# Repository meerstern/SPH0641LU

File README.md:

# SPH0641LU
The Converter board of Kicad Data for SPH0641LU

## 概要
Syntiant社製の[デジタル出力MEMSマイクSPH0641LU4H-1][1]を2.54mmピッチへ変換する基板です。  
可聴音から超音波(100Hz～80kHz)までの幅広い帯域を高感度にセンシングすることが可能です。  
超音波センサや超音波通信などに使用可能です。  
マイク穴は基板裏面の丸印部分です。  

電源電圧1.62V~3.6V、PDMデジタル出力  
セレクトピンをプルアップする場合はR2、プルダウンする場合はR1にチップ抵抗を取り付けてください。  
※接続先がDFSDMやI2S、SPI通信等のPDMマスタに対応している必要があります。　　

## 超音波マイク比較
 用途に応じて様々な製品をラインアップしています  
| 製品名 | インタフェース | アンプ搭載有無 | 用途 | 
|:-----------|:------------|:------------|:------------|
| [アナログ出力マイク][A] | アナログ | 無 | 任意のアンプ回路を使用したい場合 | 
| [可変アンプ内蔵アナログ出力マイク][B] | アナログ | 有(可変1~50倍) | 増幅率の調整が必要な場合 |	
| [アンプ内蔵アナログ出力マイク][C] |	アナログ | 有(固定50倍) | 一定した増幅が必要な場合	| 
| [デジタル出力マイク(本製品)][D] |	デジタルPDM | 不要 | フルデジタルで実装する場合やワイドレンジが必要な場合 | 

## 販売サイト
  * [スイッチサイエンス][2]
  * [Elecrow][3]

License - MIT

[1]: https://www.digikey.jp/product-detail/ja/knowles/SPH0641LU4H-1/423-1402-1-ND/5332430 "*1"
[2]: https://www.switch-science.com/products/3379
[3]: https://www.elecrow.com/digital-mems-microphone.html

[A]: https://github.com/meerstern/SPV0142LR5H
[B]: https://github.com/meerstern/SPV0142LR5H_with_VariableAmp
[C]: https://github.com/meerstern/SPV0142LR5H_with_Amp
[D]: https://github.com/meerstern/SPH0641LUAmp

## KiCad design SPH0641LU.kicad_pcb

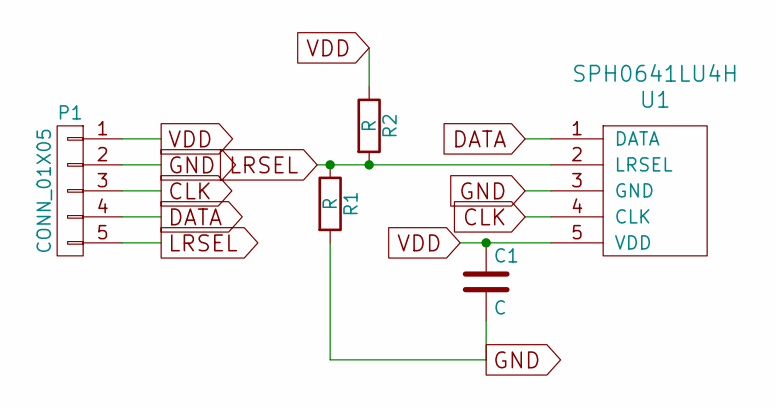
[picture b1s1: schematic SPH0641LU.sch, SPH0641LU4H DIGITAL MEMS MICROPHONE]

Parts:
C1: C; generic-SMD1608
P1: CONN_01X05; pinhead-1X05
R1, R2: R; generic-SMD1608
U1: SPH0641LU4H

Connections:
CLK: P1.3, U1.4 (CLK)
DATA: P1.4, U1.1 (DATA)
GND: C1.2, P1.2, R1.2, U1.3 (GND)
LRSEL: P1.5, R1.1, R2.2, U1.2 (LRSEL)
VDD: C1.1, P1.1, R2.1, U1.5 (VDD)

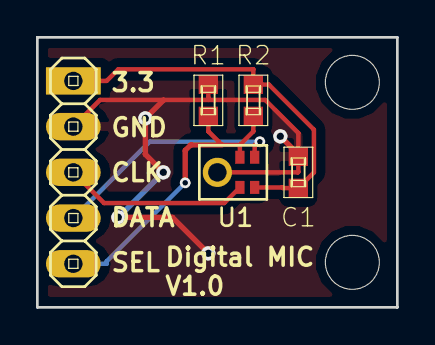
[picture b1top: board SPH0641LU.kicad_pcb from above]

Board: 2 copper layers, 20.0 x 15.0 mm, 7 parts (0 on the bottom side), 5 nets.

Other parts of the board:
REF1, REF2: MountingHole_3mm

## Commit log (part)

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2017-04-30 init
2022-12-06 Add shop link
2023-04-25 Updated store info
